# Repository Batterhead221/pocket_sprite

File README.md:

# POCKET_SPRITE

A custom ESP32-S3 handheld game console with joystick input, an action button, ST7735 color TFT display, buzzer audio, battery power, custom PCB artwork, and multiple built-in mini games.

POCKET_SPRITE is a compact original hardware project built around the Seeed Studio XIAO ESP32-S3 and a 1.8-inch ST7735 SPI TFT display. The board combines custom electronics, embedded firmware, pixel graphics, playful silkscreen art, and portable battery-powered hardware into a small handheld game device.

## Project Status

In progress. Breadboard input/display testing completed before the PCB version. Current hardware direction uses the XIAO ESP32-S3, joystick, 1.8-inch SPI TFT, A button, TFT backlight control, buzzer output, battery input through the XIAO BAT pads, and a switched 3.3V rail for game hardware.

## Features

- Seeed Studio XIAO ESP32-S3
- 1.8-inch ST7735 SPI TFT display
- Joystick input
- One action button
- TFT backlight control
- Buzzer output
- Battery input through the XIAO battery pads
- Switched 3.3V rail for game hardware
- Custom PCB outline
- Custom silkscreen artwork
- LovyanGFX display driver
- Multiple built-in games and modes

## Games / Modes

Current firmware includes:

- **Adventure**: small character-based adventure game
- **Pocket Pet**: virtual pet room with movement, jumping, ball pushing, and ball kicking
- **Dress Up**: character creator with selectable gender, hairstyles, colors, outfits, shoes, and a small playable character
- **BM Tron**: light-cycle style trail game
- **Snake**: classic snake mini game

## Hardware

| Function | Part / Notes |
|---|---|
| MCU | Seeed Studio XIAO ESP32-S3 |
| Display | 1.8-inch ST7735 SPI TFT |
| Display driver | LovyanGFX |
| Input | Joystick + one A button |
| Audio | Buzzer driven from GPIO |
| Power | Battery connected to XIAO BAT pads |
| Switched rail | XIAO_3V3 → switch → +3V3_SW |
| Board role | Portable handheld game/demo board |

## Pin Map

| XIAO Pin | Net | Function |
|---|---|---|
| D0 | JOY_SW | Joystick press |
| D1 | JOY_X | Joystick X analog |
| D2 | JOY_Y | Joystick Y analog |
| D3 | A_JUMP | A / jump button |
| D4 | CS | TFT chip select |
| D5 | DC | TFT data/command |
| D6 | RST | TFT reset |
| D7 | B-LITE | TFT backlight |
| D8 | SCK | TFT SPI clock |
| D9 | CHIRP | Buzzer drive |
| D10 | MOSI | TFT SPI MOSI |
| 3V3 | XIAO_3V3 | Regulated 3.3V from XIAO |
| GND | GND | Ground |
| BAT+ | XIAO_BAT+ | Battery positive |
| BAT- | XIAO_BAT- | Battery negative |

## Joystick Calibration

Breadboard joystick values measured during testing:

| Axis / Direction | Value / Behavior |
|---|---|
| X center | about 1970 |
| Y center | about 2020 |
| Deadzone | about 450 |
| UP | X low |
| DOWN | X high |
| LEFT | Y high |
| RIGHT | Y low |

Firmware should use calibration/deadzone handling instead of assuming perfect center values.

## Display Interface

The display is a 1.8-inch ST7735 SPI TFT.

```text
TFT CS    → D4
TFT DC    → D5
TFT RESET → D6
TFT BL    → D7 / B-LITE
TFT SCK   → D8
TFT MOSI  → D10
```

## Controls

```text
Joystick SW → D0
Joystick X  → D1
Joystick Y  → D2
A button    → D3
```

The joystick direction mapping from breadboard testing:

```text
UP    → X low
DOWN  → X high
LEFT  → Y high
RIGHT → Y low
```

## Audio Output

The buzzer output is labeled `CHIRP` and is driven from D9.

```text
D9 / CHIRP → buzzer drive
```

If the buzzer current is above the safe GPIO drive range, use a transistor or MOSFET driver instead of driving the buzzer directly from the XIAO GPIO.

## Power Design

The battery connects directly to the XIAO battery pads. The XIAO provides the regulated 3.3V rail used by the game hardware.

```text
Battery → XIAO BAT pads
XIAO_3V3 → switch → +3V3_SW
+3V3_SW → joystick / display / buzzer support hardware
```

Battery support should follow the Seeed Studio XIAO ESP32-S3 battery/BAT pad guidance for a 1S LiPo setup.

## Firmware Direction

Useful firmware modules:

- Joystick calibration
- Direction/deadzone handling
- A button input
- LovyanGFX display setup
- ST7735 display drawing helpers
- Sprite drawing and animation loop
- Game state/menu system
- Buzzer tone/beep helper
- Backlight control
- Battery-aware sleep or low-power behavior later

## Bring-Up Checklist

1. Confirm XIAO ESP32-S3 orientation and soldering.
2. Verify XIAO_3V3 and +3V3_SW behavior.
3. Test joystick X/Y ADC values.
4. Test joystick switch.
5. Test A button.
6. Test TFT display init over SPI.
7. Test TFT CS/DC/RESET behavior.
8. Test TFT backlight control on B-LITE.
9. Test buzzer output on CHIRP.
10. Run joystick-controlled movement demo.
11. Run each game mode.
12. Add battery testing only after USB-powered bring-up is stable.

## Design Notes

- Keep TFT SPI traces clean and reasonably short.
- Keep joystick analog lines away from buzzer switching where practical.
- Leave room for finger access around the joystick and A button.
- Keep silkscreen labels readable around controls.
- Treat joystick calibration as firmware data, not fixed ideal values.
- Keep the board small enough to feel handheld, not like a dinner plate with pixels.

## Repository Output Images

Expected image paths for GitHub README rendering:

```text
Outputs/
  IMG/
    3D-T.png
    3D-B.png
    SCHEMATIC.png
    L1-SIG.png
    L2-GND.png
```

## Safety / Design Note

POCKET_SPRITE is a low-voltage handheld electronics project. Verify battery polarity, switched power behavior, buzzer drive current, and display wiring before portable use.

Designed & Engineered by Brandon Shelly

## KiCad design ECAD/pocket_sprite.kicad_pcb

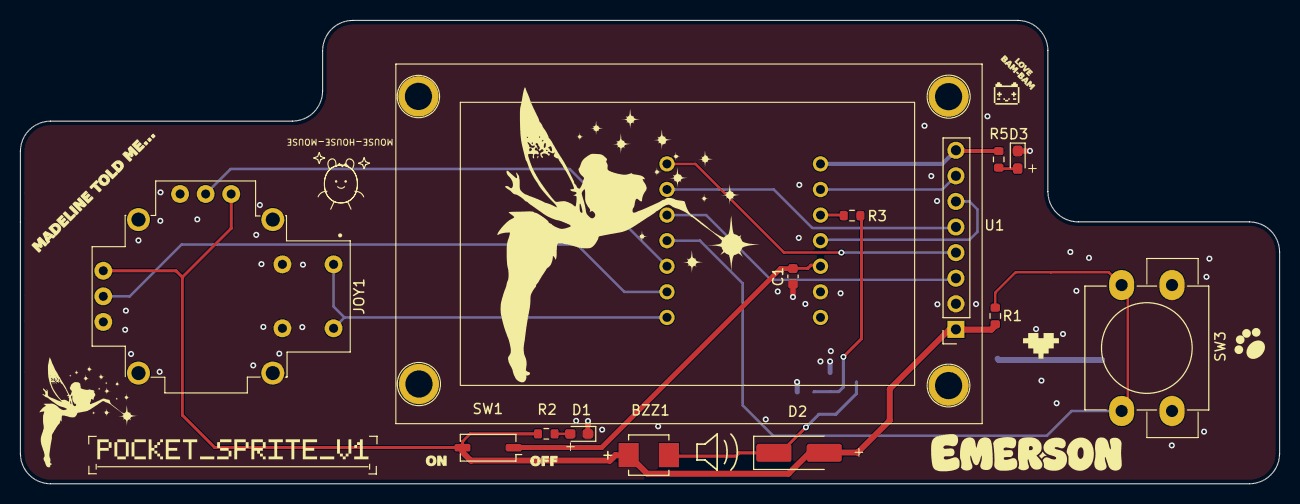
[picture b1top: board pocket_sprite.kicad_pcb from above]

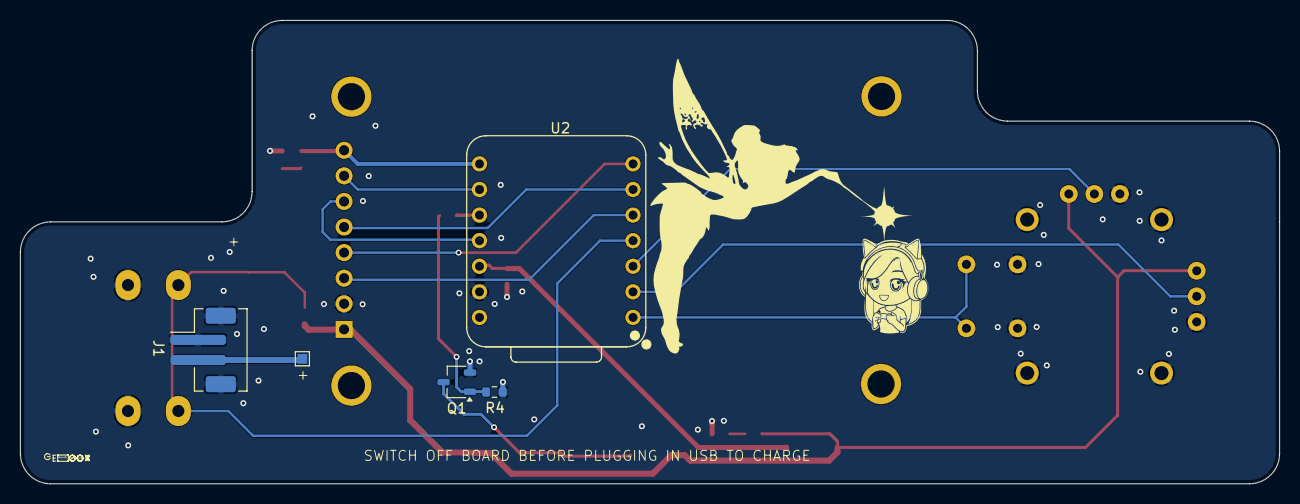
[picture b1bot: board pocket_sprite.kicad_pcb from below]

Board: 2 copper layers, 125.0 x 46.0 mm, 18 parts (5 on the bottom side), 19 nets.

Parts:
BZZ1: CMT-4023S-SMT-TR; CUI_CMT-4023S-SMT-TR
C1: 100nF; C_0603_1608Metric
D1, D3: LED_0603; D_0603_1608Metric_Pad1.05x0.95mm_HandSolder
D2: D_Schottky; D_SMA_Handsoldering
J1: Screw_Terminal_01x02; JST_PH_B2B-PH-SM4-TB_1x02-1MP_P2.00mm_Vertical
JOY1: JOYSTICK; XDCR_COM-09032_MODED
PAD1: BAT_PAD; TestPoint_Pad_1.0x1.0mm
Q1: AO3400A; TSOT-23
R1: 10K; R_0603_1608Metric
R2, R3, R5: 1K; R_0603_1608Metric
R4: 100K; R_0603_1608Metric
SW1: DS04-254-2-01BK-SMT; SW_DIP_SPSTx01_Slide_Copal_CHS-01A_W5.08mm_P1.27mm_JPin
SW3: BUTTON; Push_Button_W12mm
U1: 1.8_TFT_LCD_Display_Module; SPI_DISPLAY
U2: ESP32-S3; XIAO-ESP32_THROUGH_HOLE_PINS

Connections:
+3V3_SW: BZZ1.P, D2.2 (A), JOY1.H1 (H+), JOY1.V1 (V+), R1.2, R2.1, SW1.2 (N.O.), U1.1 (VCC)
A_JUMP: R1.1, SW3.1, U2.4 (D3)
B-LITE: R5.2, U1.8 (LED), U2.8 (RX_D7)
CHIRP: R3.2, U2.10 (D9)
CS: U1.3 (CS), U2.5 (D4)
DC: U1.5 (A0), U2.6 (D5)
GND: C1.2, D1.1 (K), D3.1 (K), J1.1, J1.3 (MP), J1.4 (MP), JOY1.B2A (SW-), JOY1.B2B (SW-), JOY1.H3 (H-), JOY1.S1 (SHIELD), JOY1.S2 (SHIELD__1), JOY1.S3 (SHIELD__2), JOY1.S4 (SHIELD__3), JOY1.V3 (V-), Q1.2 (S), R4.2, SW3.2, U1.2 (GND), U2.13 (GND)
JOY_SW: JOY1.B1A (SW+), JOY1.B1B (SW+), U2.1 (D0)
JOY_X: JOY1.H2 (H), U2.2 (D1)
JOY_Y: JOY1.V2 (V), U2.3 (D2)
MOSI: U1.6 (SDA), U2.11 (D10)
unnamed: D1.2 (A), R2.2
unnamed: BZZ1.N, D2.1 (K), Q1.3 (D)
unnamed: D3.2 (A), R5.1
unnamed: Q1.1 (G), R3.1, R4.1
RST: U1.4 (RESET), U2.7 (TX_D6)
SCK: U1.7 (SCK), U2.9 (D8)
XIAO_3V3: C1.1, SW1.1 (COM), U2.12 (VCC_3V3)
XIAO_BAT+: J1.2, PAD1.1 (1_1)

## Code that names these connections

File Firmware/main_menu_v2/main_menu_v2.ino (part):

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

// -------------------- PIN MAP --------------------
#define JOY_SW_PIN   D0
#define JOY_X_PIN    D1
#define JOY_Y_PIN    D2
#define A_BUTTON_PIN D3

#define TFT_CS       D4
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  Serial.begin(115200);
  delay(1000);

  pinMode(JOY_SW_PIN, INPUT_PULLUP);
  pinMode(A_BUTTON_PIN, INPUT_PULLUP);
  pinMode(TFT_BL, OUTPUT);
  digitalWrite(TFT_BL, HIGH);
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// ======================================================

void readControls() {
  joyX = analogRead(JOY_X_PIN);
  joyY = analogRead(JOY_Y_PIN);

  joyPressed = digitalRead(JOY_SW_PIN) == LOW;
  aPressed = digitalRead(A_BUTTON_PIN) == LOW;

  direction = "CENTER";
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
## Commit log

2026-05-20 publish
2026-05-21 redid gerbers
2026-05-24 readme
2026-05-24 next
2026-05-24 cont
